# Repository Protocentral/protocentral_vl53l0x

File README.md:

ProtoCentral VL53L0X Laser ToF sensor breakout board
====================================================
[  
*ProtoCentral VL53L0X Laser ToF sensor breakout (PC-SEN-2001)*](https://www.protocentral.com/motiondistance/1049-protocentral-vl53l0x-laser-tof-sensor-breakout.html)

[Dont have it yet? Buy one here: ProtoCentral VL53L0X Laser ToF sensor breakout (PC-SEN-2001)](https://protocentral.com/product/protocentral-vl53l0x-laser-tof-sensor-breakout/)

ST's VL53L0X is a 940 nm Laser source and a detector built in to the same chip. The result is a high accuracy Laser ranging sensor. 

This breakout board (along with the Arduino libraries) from ProtoCentral make it easier to do quick prototypes for applications that require precision ranging. Applications include obstacle detection and gesture recognition, among others. We have even used these for non-invasive liquid level detection. 

This device is a Class 1 Laser device, so is classified "Eye-safe", meaning it will not burn your corneas out !

Features
--------
* 940 nm VCSEL laser including driver
* Integrated Avalanche Photodiode
* Maximum ranging distance of up to 2 meters
* High immunity to ambient light

Includes
--------
* 1x Protocentral VL53L0X Laser tof sensor
* 1x set of breakaway headers

Repository Contents
-------------------
* **/software** - Arduino library and processing example sketch
* **/hardware** - All Eagle design files (.brd, .sch)
* **/extras** - datasheets and extras

Arduino Quickstart
------------------

* Download the [ProtoCentral VL53L0X library here](releases/download/v1.0/protocentral_vl53l0x.zip).

* Once downloaded, unzip the ZIP archive and copy the folder to your "libraries" folder in the Arduino Sketchbook folder. It is usually located in:

	* On MAC: <user_home>/Documents/Arduino/libraries
	* On Windows: <user_home>/My Documents/Arduino/libraries
	* On Linux: /home/<user_name>/sketchbook  

* After the libraries are copied, you can open the example code from File->Examples->protocentral_vl53l0x->simple_distance

* Connect the vl53l0x board to your Arduino with the following connections

	| Arduino | VL53L0X board |
	| ------- | ------------- |
	| 5V      | VIN |
	| GND     | GND |
	| SDA     | SDA |
	| SCL     | SCL |
        
Using Processing - Data Visualization Software
----------------------------------------------
 For continuous graphical data visualization as shown below, please follow the steps given in this [document](docs/using_processing.md).

License Information
===================

This product is open source! Both, our hardware and software are open source and licensed under the following licenses:

Hardware
---------

**All hardware is released under [Creative Commons Share-alike 4.0 International](http://creativecommons.org/licenses/by-sa/4.0/).**

You are free to:

* Share — copy and redistribute the material in any medium or format
* Adapt — remix, transform, and build upon the material for any purpose, even commercially.
The licensor cannot revoke these freedoms as long as you follow the license terms.

Under the following terms:

* Attribution — You must give appropriate credit, provide a link to the license, and indicate if changes were made. You may do so in any reasonable manner, but not in any way that suggests the licensor endorses you or your use.
* ShareAlike — If you remix, transform, or build upon the material, you must distribute your contributions under the same license as the original.

Software
--------

**All software is released under the MIT License(http://opensource.org/licenses/MIT).**

THE SOFTWARE IS PROVIDED "AS IS", WITHOUT WARRANTY OF ANY KIND, EXPRESS OR IMPLIED, INCLUDING BUT NOT LIMITED TO THE WARRANTIES OF MERCHANTABILITY, FITNESS FOR A PARTICULAR PURPOSE AND NONINFRINGEMENT. IN NO EVENT SHALL THE AUTHORS OR COPYRIGHT HOLDERS BE LIABLE FOR ANY CLAIM, DAMAGES OR OTHER LIABILITY, WHETHER IN AN ACTION OF CONTRACT, TORT OR OTHERWISE, ARISING FROM, OUT OF OR IN CONNECTION WITH THE SOFTWARE OR THE USE OR OTHER DEALINGS IN THE SOFTWARE.

Please check [*LICENSE.md*](LICENSE.md) for detailed license descriptions.

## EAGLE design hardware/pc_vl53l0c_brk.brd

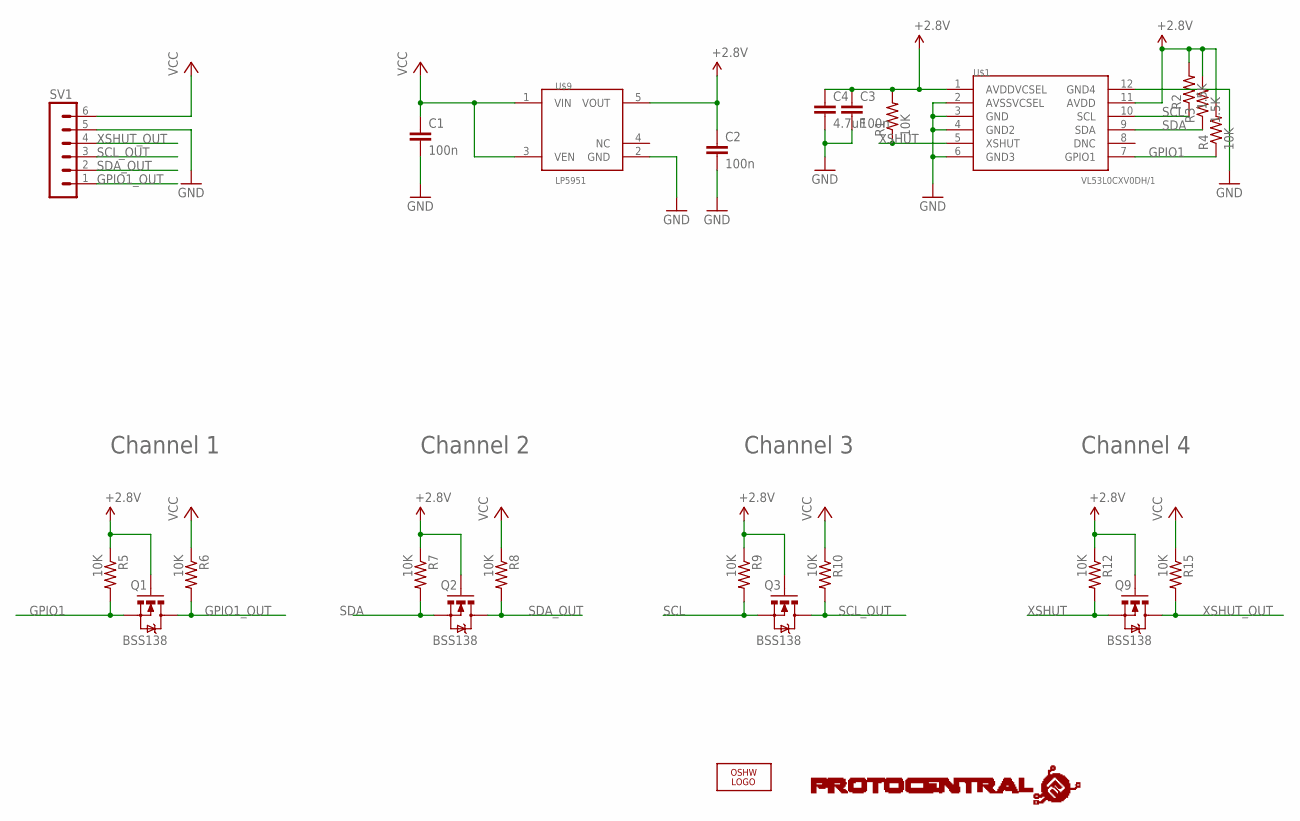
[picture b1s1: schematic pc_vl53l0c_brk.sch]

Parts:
C1, C2, C3: 100n; C0402
C4: 4.7uF; C0402
LOGO2: OSHW_LOGO_FILLX0100-NT; OSHW_FILLX100_NOTEXT
Q1, Q2, Q3, Q9: BSS138; SOT23-3
R1, R4: 10K; R0805
R2, R3: 1.5K; R0805
R5, R6, R7, R8, R9, R10, R12, R15: 10K; 0805
SV1: MA06-1
U$1: VL53L0CXV0DH/1; LGA-12
U$9: LP5951; SC70-5
U$10: PROTY_LOGO_WITH_TEXT; PROTY_WITH_TEXT

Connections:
+2.8V: C2.1, C3.1, C4.1, Q1.1 (G), Q2.1 (G), Q3.1 (G), Q9.1 (G), R1.2, R2.2, R3.2, R4.2, R5.1, R7.1, R9.1, R12.1, U$1.1 (AVDDVCSEL), U$1.11 (AVDD), U$9.5 (VOUT)
GND: C1.2, C2.2, C3.2, C4.2, SV1.5, U$1.2 (AVSSVCSEL), U$1.3 (GND), U$1.4 (GND2), U$1.6 (GND3), U$1.12 (GND4), U$9.2 (GND)
GPIO1: Q1.2 (S), R4.1, R5.2, U$1.7 (GPIO1)
GPIO1_OUT: Q1.3 (D), R6.2, SV1.1
SCL: Q3.2 (S), R2.1, R9.2, U$1.10 (SCL)
SCL_OUT: Q3.3 (D), R10.2, SV1.3
SDA: Q2.2 (S), R3.1, R7.2, U$1.9 (SDA)
SDA_OUT: Q2.3 (D), R8.2, SV1.2
VCC: C1.1, R6.1, R8.1, R10.1, R15.1, SV1.6, U$9.1 (VIN), U$9.3 (VEN)
XSHUT: Q9.2 (S), R1.1, R12.2, U$1.5 (XSHUT)
XSHUT_OUT: Q9.3 (D), R15.2, SV1.4

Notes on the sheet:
Channel 1
Channel 2
Channel 3
Channel 4

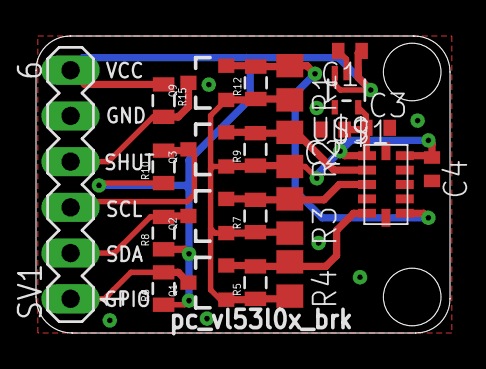
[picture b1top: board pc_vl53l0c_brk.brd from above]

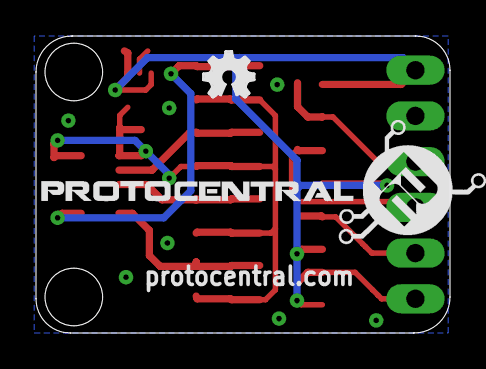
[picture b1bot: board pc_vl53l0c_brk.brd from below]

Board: 4 copper layers, 23.0 x 16.5 mm, 25 parts (2 on the bottom side), 11 nets.

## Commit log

2016-11-25 added screen capture
2016-11-25 Updated directory structure
2016-12-27 Updated license information
2017-02-13 Added interactive wreath example
2017-02-14 Updated folder structure and Readme
2017-02-14 Corrected folder structure
2017-02-14 Updated read

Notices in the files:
README.md:
CC-BY-SA-4.0
